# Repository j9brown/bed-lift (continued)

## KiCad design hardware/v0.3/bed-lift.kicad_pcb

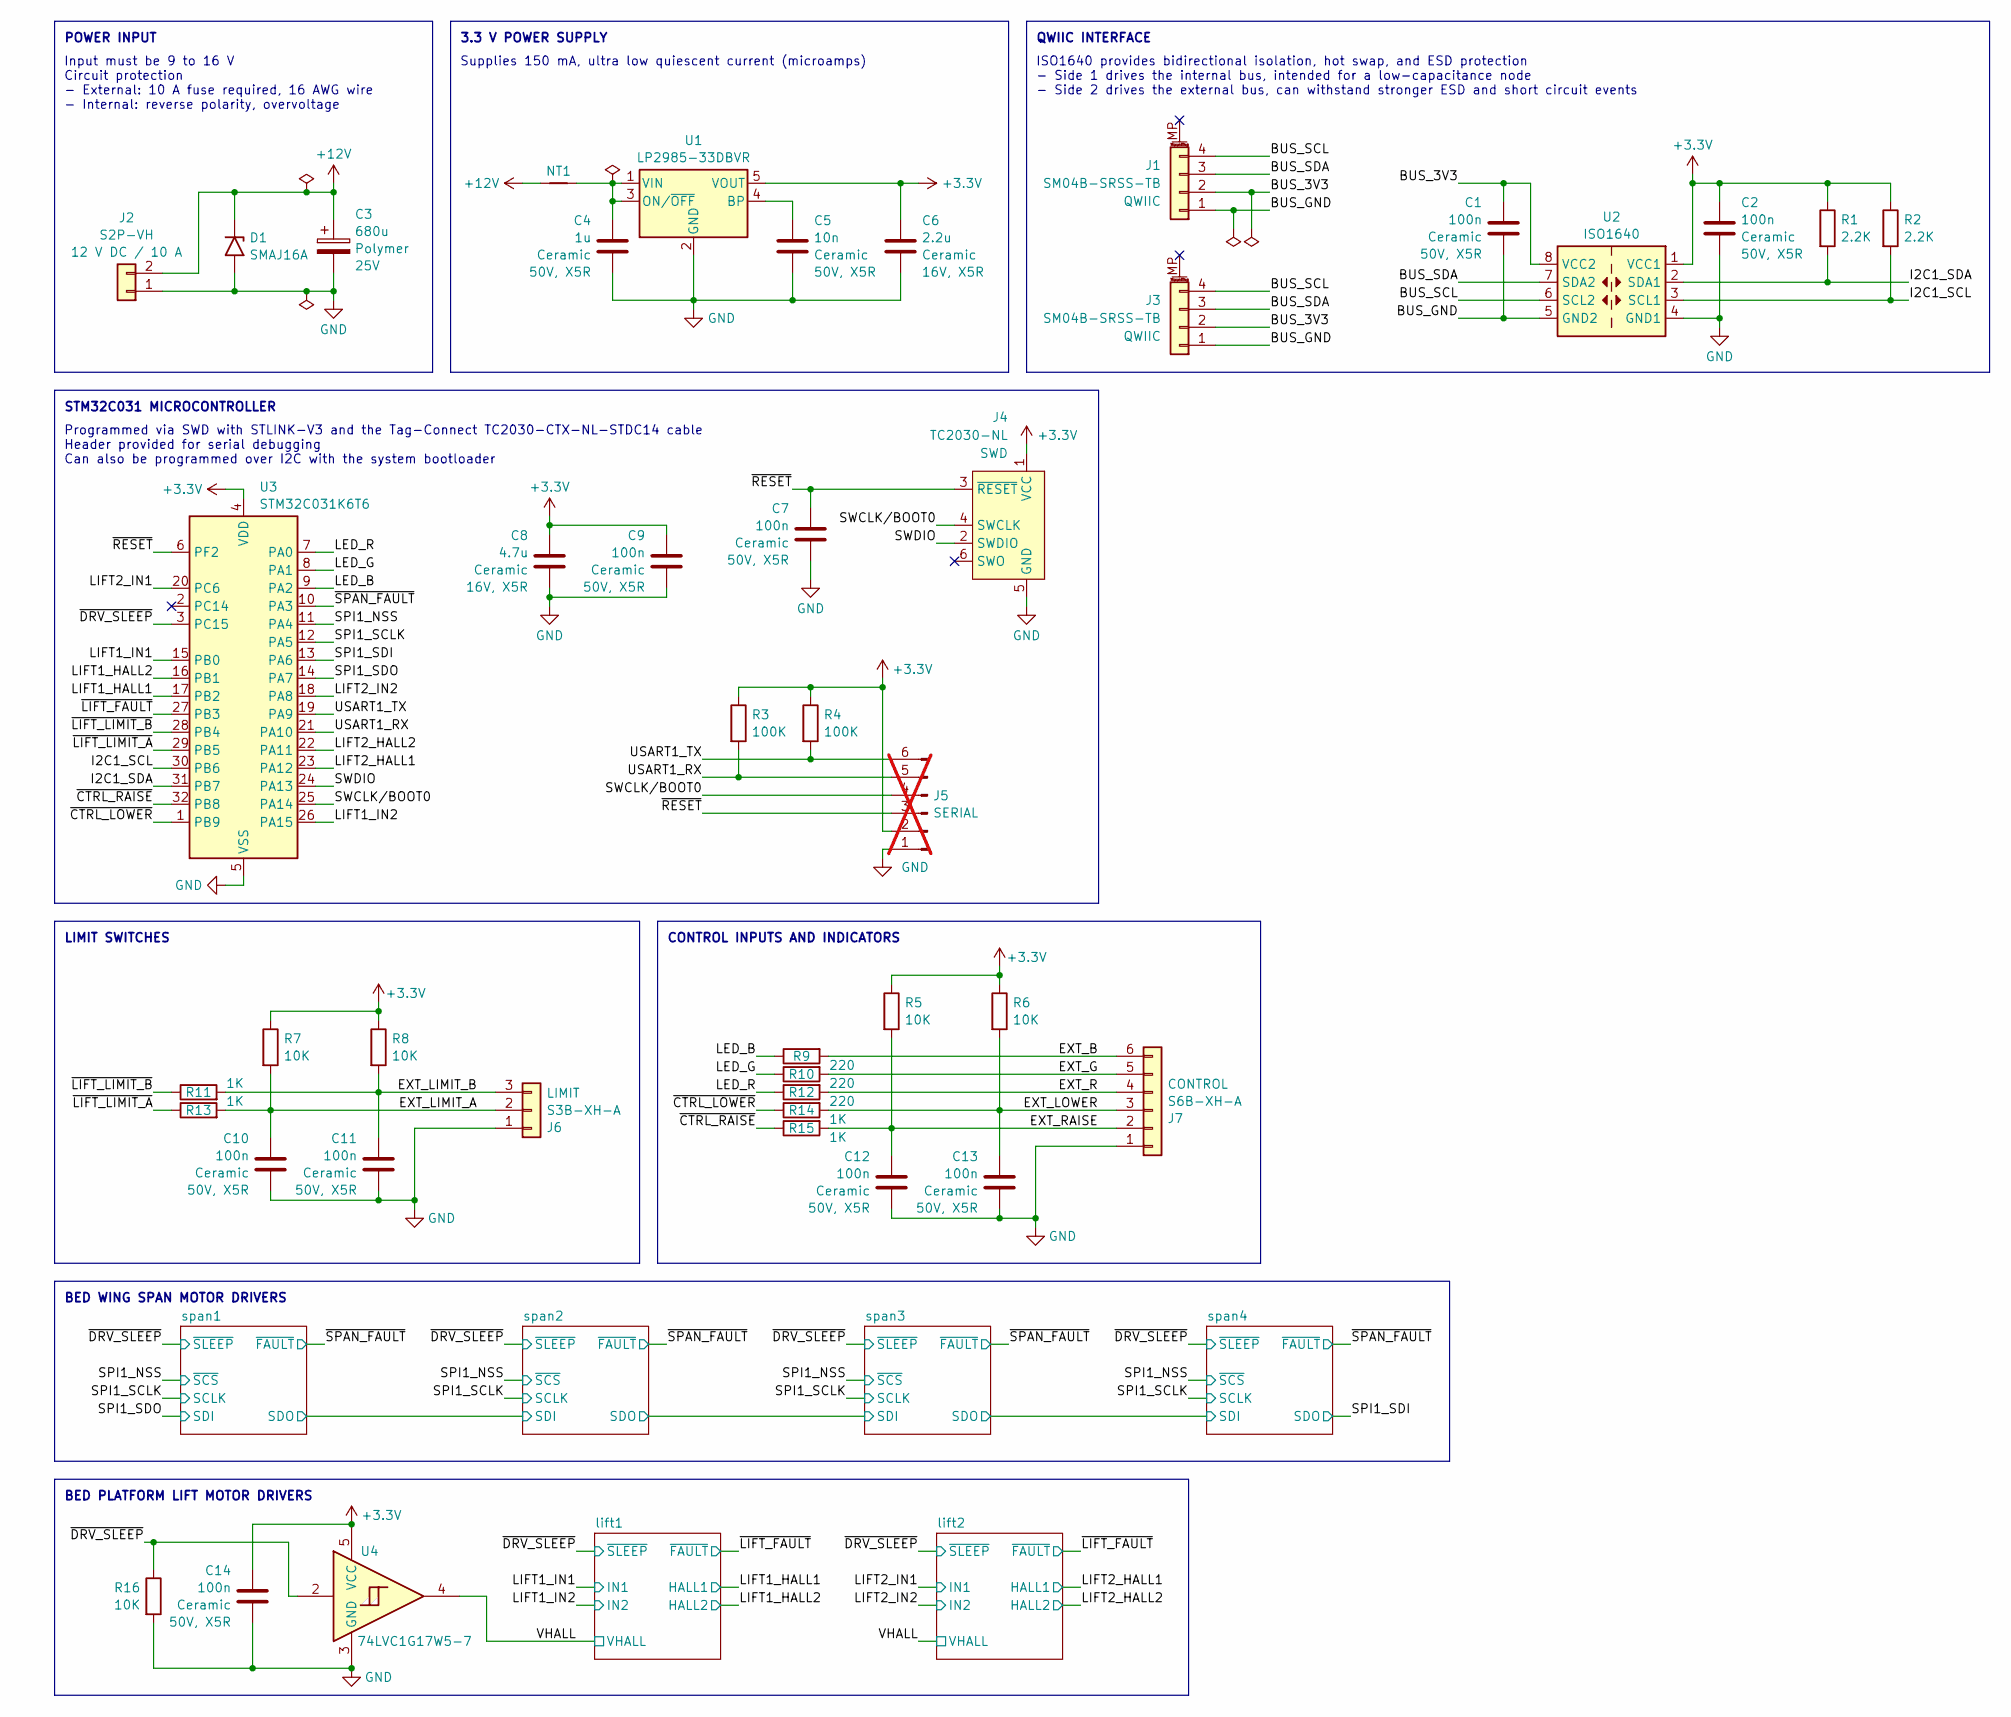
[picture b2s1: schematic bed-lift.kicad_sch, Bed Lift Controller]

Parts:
C1, C2, C7, C9, C10, C11, C12, C13, C14: 100n; C_0603_1608Metric; Rating 50V, X5R; LCSC C14663
C3: 680u; CP_Radial_D8.0mm_P3.50mm; Rating 25V; LCSC C5243855
C4: 1u; C_0603_1608Metric; Rating 50V, X5R; LCSC C15849
C5: 10n; C_0603_1608Metric; Rating 50V, X5R; LCSC C57112
C6: 2.2u; C_0603_1608Metric; Rating 16V, X5R; LCSC C23630
C8: 4.7u; C_0603_1608Metric; Rating 16V, X5R; LCSC C19666
D1: SMAJ16A; D_SMA; LCSC C74561
J1, J3: SM04B-SRSS-TB; JST_SH_SM04B-SRSS-TB_1x04-1MP_P1.00mm_Horizontal; LCSC C160404
J2: S2P-VH; JST_VH_S2P-VH_1x02_P3.96mm_Horizontal; LCSC C160355
J4: TC2030-NL; Tag-Connect_TC2030-IDC-NL_2x03_P1.27mm_Vertical
J5: PH1-06-UA; PinHeader_1x06_P2.54mm_Vertical; not fitted
J6: S3B-XH-A; JST_XH_S3B-XH-A_1x03_P2.50mm_Horizontal; LCSC C157928
J7: S6B-XH-A; JST_XH_S6B-XH-A_1x06_P2.50mm_Horizontal; LCSC C157919
NT1: NetTie_2; NetTie-2_SMD_Pad0.4mm
R1, R2: 2.2K; R_0603_1608Metric; LCSC C4190
R3, R4: 100K; R_0603_1608Metric; LCSC C25803
R5, R6, R7, R8, R16: 10K; R_0603_1608Metric; LCSC C25804
R9, R10, R12: 220; R_0603_1608Metric; LCSC C22962
R11, R13, R14, R15: 1K; R_0603_1608Metric; LCSC C21190
U1: LP2985-33DBVR; SOT-23-5; LCSC C95414
U2: ISO1640; SOIC-8_3.9x4.9mm_P1.27mm; LCSC C5122339
U3: STM32C031K6T6; LQFP-32_7x7mm_P0.8mm; LCSC C5456169
U4: 74LVC1G17W5-7; SOT-23-5; LCSC C151394

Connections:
+3.3V: C2.1, C6.2, C8.1, C9.1, C14.1, J4.1 (VCC), J5.2, R1.1, R2.1, R3.1, R4.1, R5.1, R6.1, R7.1, R8.1, U1.5 (VOUT), U2.1 (VCC1), U3.4 (VDD), U4.5 (VCC); also elsewhere on the board
+12V: C3.1, D1.1 (A1), J2.2, NT1.1; also elsewhere on the board
/BUS_3V3: C1.1, J1.2, J3.2, U2.8 (VCC2)
/BUS_GND: C1.2, J1.1, J3.1, U2.5 (GND2)
/BUS_SCL: J1.4, J3.4, U2.6 (SCL2)
/BUS_SDA: J1.3, J3.3, U2.7 (SDA2)
/EXT_B: J7.6, R9.2
/EXT_G: J7.5, R10.2
/EXT_LIMIT_A: C10.1, J6.2, R7.2, R13.2
/EXT_LIMIT_B: C11.1, J6.3, R8.2, R11.2
/EXT_LOWER: C13.1, J7.3, R6.2, R14.2
/EXT_R: J7.4, R12.2
/EXT_RAISE: C12.1, J7.2, R5.2, R15.2
/I2C1_SCL: R2.2, U2.3 (SCL1), U3.30 (PB6)
/I2C1_SDA: R1.2, U2.2 (SDA1), U3.31 (PB7)
/LED_B: R9.1, U3.9 (PA2)
/LED_G: R10.1, U3.8 (PA1)
/LED_R: R12.1, U3.7 (PA0)
/LIFT1_HALL1: U3.17 (PB2); also elsewhere on the board
/LIFT1_HALL2: U3.16 (PB1); also elsewhere on the board
/LIFT1_IN1: U3.15 (PB0); also elsewhere on the board
/LIFT1_IN2: U3.26 (PA15); also elsewhere on the board
/LIFT2_HALL1: U3.23 (PA12); also elsewhere on the board
/LIFT2_HALL2: U3.22 (PA11); also elsewhere on the board
/LIFT2_IN1: U3.20 (PC6); also elsewhere on the board
/LIFT2_IN2: U3.18 (PA8); also elsewhere on the board
/SPI1_NSS: U3.11 (PA4); also elsewhere on the board
/SPI1_SCLK: U3.12 (PA5); also elsewhere on the board
/SPI1_SDI: U3.13 (PA6); also elsewhere on the board
/SPI1_SDO: U3.14 (PA7); also elsewhere on the board
/SWCLK/BOOT0: J4.4 (SWCLK), J5.4, U3.25 (PA14)
/SWDIO: J4.2 (SWDIO), U3.24 (PA13)
/USART1_RX: J5.5, R3.2, U3.21 (PA10)
/USART1_TX: J5.6, R4.2, U3.19 (PA9)
/VHALL: U4.4; also elsewhere on the board
/~CTRL_LOWER: R14.1, U3.1 (PB9)
/~CTRL_RAISE: R15.1, U3.32 (PB8)
/~DRV_SLEEP: R16.1, U3.3 (PC15), U4.2; also elsewhere on the board
/~LIFT_FAULT: U3.27 (PB3); also elsewhere on the board
/~LIFT_LIMIT_A: R13.1, U3.29 (PB5)
/~LIFT_LIMIT_B: R11.1, U3.28 (PB4)
/~RESET: C7.1, J4.3 (~RESET), J5.3, U3.6 (PF2)
/~SPAN_FAULT: U3.10 (PA3); also elsewhere on the board
GND: C2.2, C3.2, C4.2, C5.1, C6.1, C7.2, C8.2, C9.2, C10.2, C11.2, C12.2, C13.2, C14.2, D1.2 (A2), J2.1, J4.5 (GND), J5.1, J6.1, J7.1, R16.2, U1.2 (GND), U2.4 (GND1), U3.5 (VSS), U4.3 (GND); also elsewhere on the board
unnamed: C5.2, U1.4 (BP)
unnamed: C4.1, NT1.2, U1.1 (VIN), U1.3 (ON/~OFF)

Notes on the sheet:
Programmed via SWD with STLINK-V3 and the Tag-Connect TC2030-CTX-NL-STDC14 cable Header provided for serial debugging Can also be programmed over I2C with the system bootloader
Supplies 150 mA, ultra low quiescent current (microamps)
LIMIT SWITCHES
POWER INPUT
BED WING SPAN MOTOR DRIVERS
STM32C031 MICROCONTROLLER
3.3 V POWER SUPPLY
QWIIC INTERFACE
CONTROL INPUTS AND INDICATORS
Input must be 9 to 16 V Circuit protection - External: 10 A fuse required, 16 AWG wire - Internal: reverse polarity, overvoltage
ISO1640 provides bidirectional isolation, hot swap, and ESD protection - Side 1 drives the internal bus, intended for a low-capacitance node - Side 2 drives the external bus, can withstand stronger ESD and short circuit events
BED PLATFORM LIFT MOTOR DRIVERS

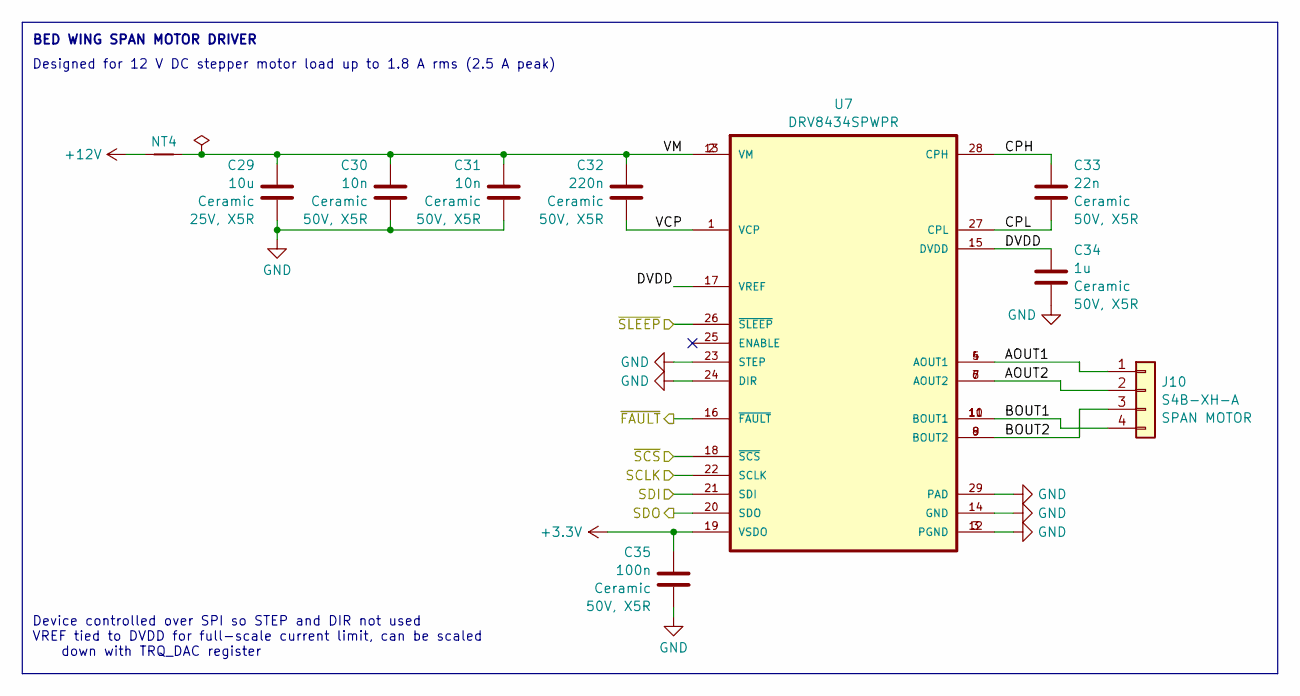
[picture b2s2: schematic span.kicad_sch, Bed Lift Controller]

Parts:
C29: 10u; C_0805_2012Metric; Rating 25V, X5R; LCSC C15850
C30, C31: 10n; C_0603_1608Metric; Rating 50V, X5R; LCSC C57112
C32: 220n; C_0603_1608Metric; Rating 50V, X5R; LCSC C1603
C33: 22n; C_0603_1608Metric; Rating 50V, X5R; LCSC C21122
C34: 1u; C_0603_1608Metric; Rating 50V, X5R; LCSC C15849
C35: 100n; C_0603_1608Metric; Rating 50V, X5R; LCSC C14663
J10: S4B-XH-A; JST_XH_S4B-XH-A_1x04_P2.50mm_Horizontal; LCSC C157925
NT4: NetTie_2; NetTie-2_SMD_Pad1.5mm
U7: DRV8434SPWPR; HTSSOP-28 PWP0028M; LCSC C3681202

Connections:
+3.3V: C35.1, U7.19 (VSDO); also elsewhere on the board
+12V: NT4.1; also elsewhere on the board
/SPI1_NSS: U7.18 (~SCS); also elsewhere on the board
/SPI1_SCLK: U7.22 (SCLK); also elsewhere on the board
/SPI1_SDO: U7.21 (SDI); also elsewhere on the board
/span1/AOUT1: J10.1, U7.4 (AOUT1), U7.5 (AOUT1)
/span1/AOUT2: J10.2, U7.6 (AOUT2), U7.7 (AOUT2)
/span1/BOUT1: J10.4, U7.10 (BOUT1), U7.11 (BOUT1)
/span1/BOUT2: J10.3, U7.8 (BOUT2), U7.9 (BOUT2)
/span1/CPH: C33.1, U7.28 (CPH)
/span1/CPL: C33.2, U7.27 (CPL)
/span1/DVDD: C34.1, U7.15 (DVDD), U7.17 (VREF)
/span1/SDO: U7.20 (SDO); also elsewhere on the board
/span1/VCP: C32.2, U7.1 (VCP)
/span1/VM: C29.2, C30.1, C31.1, C32.1, NT4.2, U7.2 (VM), U7.13 (VM)
/~DRV_SLEEP: U7.26 (~SLEEP); also elsewhere on the board
/~SPAN_FAULT: U7.16 (~FAULT); also elsewhere on the board
GND: C29.1, C30.2, C31.2, C34.2, C35.2, U7.3 (PGND), U7.12 (PGND), U7.14 (GND), U7.23 (STEP), U7.24 (DIR), U7.29 (PAD); also elsewhere on the board

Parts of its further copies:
C36, C43, C50: 10u; C_0805_2012Metric; Rating 25V, X5R; LCSC C15850
C37, C38, C44, C45, C51, C52: 10n; C_0603_1608Metric; Rating 50V, X5R; LCSC C57112
C39, C46, C53: 220n; C_0603_1608Metric; Rating 50V, X5R; LCSC C1603
C40, C47, C54: 22n; C_0603_1608Metric; Rating 50V, X5R; LCSC C21122
C41, C48, C55: 1u; C_0603_1608Metric; Rating 50V, X5R; LCSC C15849
C42, C49, C56: 100n; C_0603_1608Metric; Rating 50V, X5R; LCSC C14663
J11, J12, J13: S4B-XH-A; JST_XH_S4B-XH-A_1x04_P2.50mm_Horizontal; LCSC C157925
NT5, NT6, NT7: NetTie_2; NetTie-2_SMD_Pad1.5mm
U8, U9, U10: DRV8434SPWPR; HTSSOP-28 PWP0028M; LCSC C3681202

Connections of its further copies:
+3.3V: C42.1, C49.1, C56.1, U8.19 (VSDO), U9.19 (VSDO), U10.19 (VSDO); also elsewhere on the board
+12V: NT5.1, NT6.1, NT7.1; also elsewhere on the board
/SPI1_NSS: U8.18 (~SCS), U9.18 (~SCS), U10.18 (~SCS); also elsewhere on the board
/SPI1_SCLK: U8.22 (SCLK), U9.22 (SCLK), U10.22 (SCLK); also elsewhere on the board
/SPI1_SDI: U10.20 (SDO); also elsewhere on the board
/span1/SDO: U8.21 (SDI); also elsewhere on the board
/span2/AOUT1: J11.1, U8.4 (AOUT1), U8.5 (AOUT1)
/span2/AOUT2: J11.2, U8.6 (AOUT2), U8.7 (AOUT2)
/span2/BOUT1: J11.4, U8.10 (BOUT1), U8.11 (BOUT1)
/span2/BOUT2: J11.3, U8.8 (BOUT2), U8.9 (BOUT2)
/span2/CPH: C40.1, U8.28 (CPH)
/span2/CPL: C40.2, U8.27 (CPL)
/span2/DVDD: C41.1, U8.15 (DVDD), U8.17 (VREF)
/span2/SDO: U8.20 (SDO), U9.21 (SDI)
/span2/VCP: C39.2, U8.1 (VCP)
/span2/VM: C36.2, C37.1, C38.1, C39.1, NT5.2, U8.2 (VM), U8.13 (VM)
/span3/AOUT1: J12.1, U9.4 (AOUT1), U9.5 (AOUT1)
/span3/AOUT2: J12.2, U9.6 (AOUT2), U9.7 (AOUT2)
/span3/BOUT1: J12.4, U9.10 (BOUT1), U9.11 (BOUT1)
/span3/BOUT2: J12.3, U9.8 (BOUT2), U9.9 (BOUT2)
/span3/CPH: C47.1, U9.28 (CPH)
/span3/CPL: C47.2, U9.27 (CPL)
/span3/DVDD: C48.1, U9.15 (DVDD), U9.17 (VREF)
/span3/SDO: U9.20 (SDO), U10.21 (SDI)
/span3/VCP: C46.2, U9.1 (VCP)
/span3/VM: C43.2, C44.1, C45.1, C46.1, NT6.2, U9.2 (VM), U9.13 (VM)
/span4/AOUT1: J13.1, U10.4 (AOUT1), U10.5 (AOUT1)
/span4/AOUT2: J13.2, U10.6 (AOUT2), U10.7 (AOUT2)
/span4/BOUT1: J13.4, U10.10 (BOUT1), U10.11 (BOUT1)
/span4/BOUT2: J13.3, U10.8 (BOUT2), U10.9 (BOUT2)
/span4/CPH: C54.1, U10.28 (CPH)
/span4/CPL: C54.2, U10.27 (CPL)
/span4/DVDD: C55.1, U10.15 (DVDD), U10.17 (VREF)
/span4/VCP: C53.2, U10.1 (VCP)
/span4/VM: C50.2, C51.1, C52.1, C53.1, NT7.2, U10.2 (VM), U10.13 (VM)
/~DRV_SLEEP: U8.26 (~SLEEP), U9.26 (~SLEEP), U10.26 (~SLEEP); also elsewhere on the board
/~SPAN_FAULT: U8.16 (~FAULT), U9.16 (~FAULT), U10.16 (~FAULT); also elsewhere on the board
GND: C36.1, C37.2, C38.2, C41.2, C42.2, C43.1, C44.2, C45.2, C48.2, C49.2, C50.1, C51.2, C52.2, C55.2, C56.2, U8.3 (PGND), U8.12 (PGND), U8.14 (GND), U8.23 (STEP), U8.24 (DIR), U8.29 (PAD), U9.3 (PGND), U9.12 (PGND), U9.14 (GND), U9.23 (STEP), U9.24 (DIR), U9.29 (PAD), U10.3 (PGND), U10.12 (PGND), U10.14 (GND), U10.23 (STEP), U10.24 (DIR), U10.29 (PAD); also elsewhere on the board

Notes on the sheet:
Designed for 12 V DC stepper motor load up to 1.8 A rms (2.5 A peak)
BED WING SPAN MOTOR DRIVER
Device controlled over SPI so STEP and DIR not used VREF tied to DVDD for full-scale current limit, can be scaled down with TRQ_DAC register

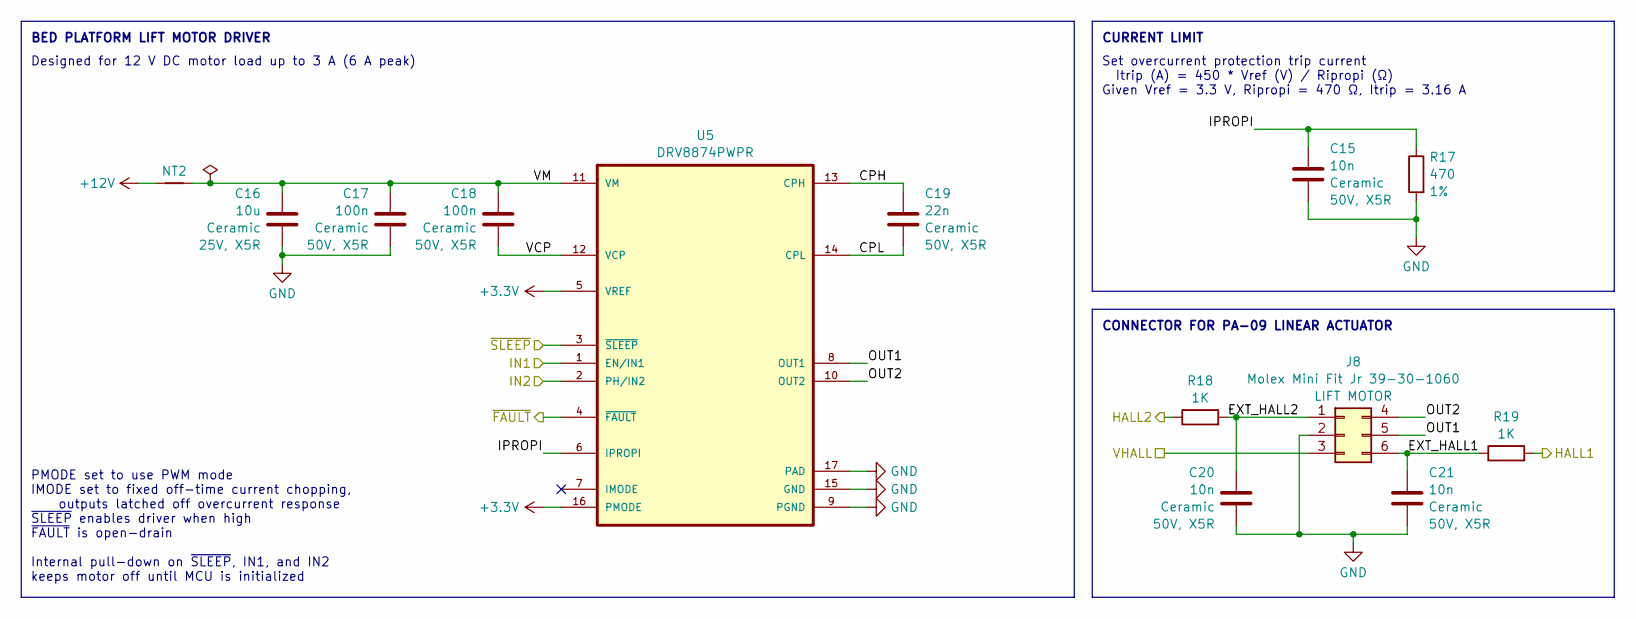
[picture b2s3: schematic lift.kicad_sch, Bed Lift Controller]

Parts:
C15, C20, C21: 10n; C_0603_1608Metric; Rating 50V, X5R; LCSC C57112
C16: 10u; C_0805_2012Metric; Rating 25V, X5R; LCSC C15850
C17, C18: 100n; C_0603_1608Metric; Rating 50V, X5R; LCSC C14663
C19: 22n; C_0603_1608Metric; Rating 50V, X5R; LCSC C21122
J8: Molex Mini Fit Jr 39-30-1060; MOLEX_39301060; LCSC C114098
NT2: NetTie_2; NetTie-2_SMD_Pad2.5mm
R17: 470; R_0603_1608Metric; Rating 1%; LCSC C23179
R18, R19: 1K; R_0603_1608Metric; LCSC C21190
U5: DRV8874PWPR; HTSSOP-16 PWP0016J; LCSC C1855818

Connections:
+3.3V: U5.5 (VREF), U5.16 (PMODE); also elsewhere on the board
+12V: NT2.1; also elsewhere on the board
/LIFT1_HALL1: R19.2; also elsewhere on the board
/LIFT1_HALL2: R18.1; also elsewhere on the board
/LIFT1_IN1: U5.1 (EN/IN1); also elsewhere on the board
/LIFT1_IN2: U5.2 (PH/IN2); also elsewhere on the board
/VHALL: J8.3; also elsewhere on the board
/lift1/CPH: C19.1, U5.13 (CPH)
/lift1/CPL: C19.2, U5.14 (CPL)
/lift1/EXT_HALL1: C21.1, J8.6, R19.1
/lift1/EXT_HALL2: C20.1, J8.1, R18.2
/lift1/IPROPI: C15.1, R17.1, U5.6 (IPROPI)
/lift1/OUT1: J8.5, U5.8 (OUT1)
/lift1/OUT2: J8.4, U5.10 (OUT2)
/lift1/VCP: C18.2, U5.12 (VCP)
/lift1/VM: C16.2, C17.1, C18.1, NT2.2, U5.11 (VM)
/~DRV_SLEEP: U5.3 (~SLEEP); also elsewhere on the board
/~LIFT_FAULT: U5.4 (~FAULT); also elsewhere on the board
GND: C15.2, C16.1, C17.2, C20.2, C21.2, J8.2, R17.2, U5.9 (PGND), U5.15 (GND), U5.17 (PAD); also elsewhere on the board

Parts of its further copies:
C22, C27, C28: 10n; C_0603_1608Metric; Rating 50V, X5R; LCSC C57112
C23: 10u; C_0805_2012Metric; Rating 25V, X5R; LCSC C15850
C24, C25: 100n; C_0603_1608Metric; Rating 50V, X5R; LCSC C14663
C26: 22n; C_0603_1608Metric; Rating 50V, X5R; LCSC C21122
J9: Molex Mini Fit Jr 39-30-1060; MOLEX_39301060; LCSC C114098
NT3: NetTie_2; NetTie-2_SMD_Pad2.5mm
R20: 470; R_0603_1608Metric; Rating 1%; LCSC C23179
R21, R22: 1K; R_0603_1608Metric; LCSC C21190
U6: DRV8874PWPR; HTSSOP-16 PWP0016J; LCSC C1855818

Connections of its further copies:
+3.3V: U6.5 (VREF), U6.16 (PMODE); also elsewhere on the board
+12V: NT3.1; also elsewhere on the board
/LIFT2_HALL1: R22.2; also elsewhere on the board
/LIFT2_HALL2: R21.1; also elsewhere on the board
/LIFT2_IN1: U6.1 (EN/IN1); also elsewhere on the board
/LIFT2_IN2: U6.2 (PH/IN2); also elsewhere on the board
/VHALL: J9.3; also elsewhere on the board
/lift2/CPH: C26.1, U6.13 (CPH)
/lift2/CPL: C26.2, U6.14 (CPL)
/lift2/EXT_HALL1: C28.1, J9.6, R22.1
/lift2/EXT_HALL2: C27.1, J9.1, R21.2
/lift2/IPROPI: C22.1, R20.1, U6.6 (IPROPI)
/lift2/OUT1: J9.5, U6.8 (OUT1)
/lift2/OUT2: J9.4, U6.10 (OUT2)
/lift2/VCP: C25.2, U6.12 (VCP)
/lift2/VM: C23.2, C24.1, C25.1, NT3.2, U6.11 (VM)
/~DRV_SLEEP: U6.3 (~SLEEP); also elsewhere on the board
/~LIFT_FAULT: U6.4 (~FAULT); also elsewhere on the board
GND: C22.2, C23.1, C24.2, C27.2, C28.2, J9.2, R20.2, U6.9 (PGND), U6.15 (GND), U6.17 (PAD); also elsewhere on the board

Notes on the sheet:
CONNECTOR FOR PA-09 LINEAR ACTUATOR
PMODE set to use PWM mode IMODE set to fixed off-time current chopping, outputs latched off overcurrent response ~{SLEEP} enables driver when high ~{FAULT} is open-drain Internal pull-down on ~{SLEEP}, IN1, and IN2 keeps motor off until MCU is initialized
BED PLATFORM LIFT MOTOR DRIVER
CURRENT LIMIT
Designed for 12 V DC motor load up to 3 A (6 A peak)
Set overcurrent protection trip current Itrip (A) = 450 * Vref (V) / Ripropi (Ω) Given Vref = 3.3 V, Ripropi = 470 Ω, Itrip = 3.16 A

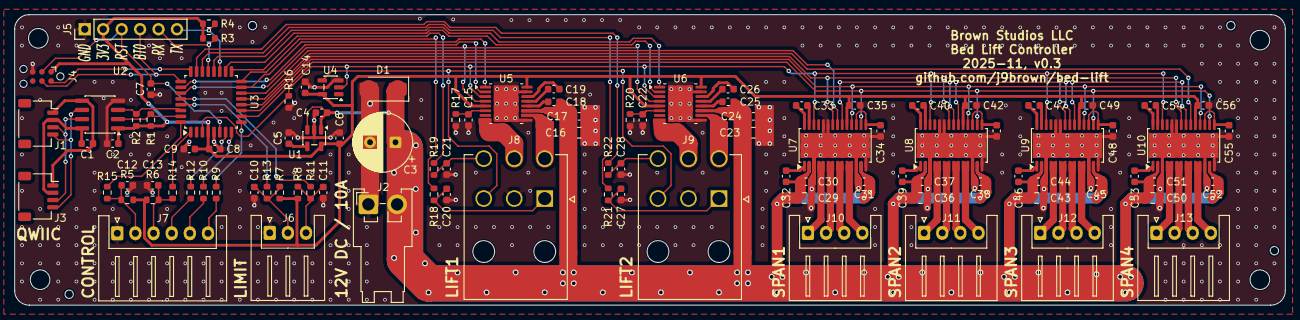
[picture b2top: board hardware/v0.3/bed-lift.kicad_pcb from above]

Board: 4 copper layers, 175.0 x 40.0 mm, 117 parts (1 on the bottom side), 103 nets.

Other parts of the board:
MP1, MP2, MP3, MP4: MountingHole_2.7mm_M2.5
TH1, TH1#2, TH1#3, TH1#4: JLCPCB_PCBA_Tooling_Hole

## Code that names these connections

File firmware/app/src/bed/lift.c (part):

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#define LIFT_LIMIT_DEBOUNCE_MS (50)
#define LIFT_LIMIT_DEBOUNCE_CYCLES (uint32_t)((uint64_t)CONFIG_SYS_CLOCK_HW_CYCLES_PER_SEC * LIFT_LIMIT_DEBOUNCE_MS / 1000)

static const struct gpio_dt_spec lift_limit_a_gpio = GPIO_DT_SPEC_GET(ZEPHYR_USER_NODE, lift_limit_a_gpios);
static const struct gpio_dt_spec lift_limit_b_gpio = GPIO_DT_SPEC_GET(ZEPHYR_USER_NODE, lift_limit_b_gpios);

enum lift_limit_state {
    LIFT_LIMIT_BELOW_SAFE_ZONE = 0b11,
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// This function must be called on every timer tick (before the cycle counter rolls over).
static void lift_limit_update_l(uint32_t cycle) {
    gpio_port_value_t value = 0;
    gpio_port_get(lift_limit_a_gpio.port, &value);
    enum lift_limit_state state =
            (IS_BIT_SET(value, lift_limit_a_gpio.pin) ? 0b01 : 0) |
            (IS_BIT_SET(value, lift_limit_b_gpio.pin) ? 0b10 : 0);
    if (state != lift_limit_data.raw_state) {
        lift_limit_data.raw_state = state;
        lift_limit_data.raw_change_cycle = cycle;
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
#define LIFT_HALL_PULSES_PER_INCH (660)

static const struct gpio_dt_spec lift1_hall1_gpio = GPIO_DT_SPEC_GET(ZEPHYR_USER_NODE, lift1_hall1_gpios);
static const struct gpio_dt_spec lift1_hall2_gpio = GPIO_DT_SPEC_GET(ZEPHYR_USER_NODE, lift1_hall2_gpios);
static const struct gpio_dt_spec lift2_hall1_gpio = GPIO_DT_SPEC_GET(ZEPHYR_USER_NODE, lift2_hall1_gpios);
static const struct gpio_dt_spec lift2_hall2_gpio = GPIO_DT_SPEC_GET(ZEPHYR_USER_NODE, lift2_hall2_gpios);

struct lift_hall_data {
    struct gpio_callback gpio_callback;
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    gpio_port_value_t value = 0;
    gpio_port_get(port, &value);
    unsigned bits =
            (IS_BIT_SET(value, lift1_hall1_gpio.pin) ? 0b10 : 0) |
            (IS_BIT_SET(value, lift1_hall2_gpio.pin) ? 0b01 : 0);
    atomic_add(&lift1_hall_data.isr_position, LIFT_HALL_QUADRATURE[(lift1_hall_data.isr_bits << 2) | bits]);
    lift1_hall_data.isr_bits = bits;
}
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    gpio_port_value_t value = 0;
    gpio_port_get(port, &value);
    unsigned bits =
            (IS_BIT_SET(value, lift2_hall1_gpio.pin) ? 0b10 : 0) |
            (IS_BIT_SET(value, lift2_hall2_gpio.pin) ? 0b01 : 0);
    atomic_add(&lift2_hall_data.isr_position, LIFT_HALL_QUADRATURE[(lift2_hall_data.isr_bits << 2) | bits]);
    lift2_hall_data.isr_bits = bits;
}
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 * LIFT MOTOR CONTROLLER
 */

static const struct gpio_dt_spec lift_fault_gpio = GPIO_DT_SPEC_GET(ZEPHYR_USER_NODE, lift_fault_gpios);
static const struct gpio_dt_spec lift_sleep_gpio = GPIO_DT_SPEC_GET(ZEPHYR_USER_NODE, lift_sleep_gpios);

#define LIFT_IN_TIMER_NUMBER 1
#define LIFT_IN_TIMER_NODE DT_NODELABEL(_CONCAT(timers, LIFT_IN_TIMER_NUMBER))
#define LIFT_IN_TIMER _CONCAT(TIM, LIFT_IN_TIMER_NUMBER)

static const struct pwm_dt_spec lift1_in1_pwm = PWM_DT_SPEC_GET_BY_IDX(DT_NODELABEL(lift1_in1), 0);
static const struct pwm_dt_spec lift1_in2_pwm = PWM_DT_SPEC_GET_BY_IDX(DT_NODELABEL(lift1_in2), 0);
static const struct pwm_dt_spec lift2_in1_pwm = PWM_DT_SPEC_GET_BY_IDX(DT_NODELABEL(lift2_in1), 0);
static const struct pwm_dt_spec lift2_in2_pwm = PWM_DT_SPEC_GET_BY_IDX(DT_NODELABEL(lift2_in2), 0);

static const struct device *lift_loop_tick_dev = DEVICE_DT_GET(DT_NODELABEL(lift_loop_tick));

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static struct lift_loop_data lift_loop_data;

static int lift_has_fault(void) {
	return gpio_pin_get_dt(&lift_fault_gpio);
}

static void lift_loop_tick_handler(const struct device *dev, void *user_data) {
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
int lift_init(void) {
    int err;
    const struct device *lift_fault_port = lift_fault_gpio.port;
    const struct device *lift_sleep_port = lift_sleep_gpio.port;
    const struct device *lift_limit_port = lift_limit_a_gpio.port;
    const struct device *lift1_hall_port = lift1_hall1_gpio.port;
    const struct device *lift2_hall_port = lift2_hall1_gpio.port;
    const struct device *lift_in_dev = lift1_in1_pwm.dev;
    const uint32_t lift_in_period_ns = lift1_in1_pwm.period;
    if (lift_limit_port != lift_limit_b_gpio.port ||
            lift1_hall_port != lift1_hall2_gpio.port ||
            lift2_hall_port != lift2_hall2_gpio.port ||
            lift1_in2_pwm.dev != lift_in_dev || lift1_in2_pwm.period != lift_in_period_ns ||
            lift2_in1_pwm.dev != lift_in_dev || lift2_in1_pwm.period != lift_in_period_ns ||
            lift2_in2_pwm.dev != lift_in_dev || lift2_in2_pwm.period != lift_in_period_ns) {
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            !device_is_ready(lift_in_dev)) {
        return -ENODEV;
    }
    if ((err = gpio_pin_configure_dt(&lift_fault_gpio, GPIO_INPUT)) ||
            (err = gpio_pin_configure_dt(&lift_sleep_gpio, GPIO_OUTPUT_ACTIVE)) ||
            (err = gpio_pin_configure_dt(&lift_limit_a_gpio, GPIO_INPUT)) ||
            (err = gpio_pin_configure_dt(&lift_limit_b_gpio, GPIO_INPUT)) ||
            (err = gpio_pin_configure_dt(&lift1_hall1_gpio, GPIO_INPUT)) ||
            (err = gpio_pin_configure_dt(&lift1_hall2_gpio, GPIO_INPUT)) ||
            (err = gpio_pin_configure_dt(&lift2_hall1_gpio, GPIO_INPUT)) ||
            (err = gpio_pin_configure_dt(&lift2_hall2_gpio, GPIO_INPUT))) {
        return err;
    }
    if ((err = gpio_pin_interrupt_configure_dt(&lift1_hall1_gpio, GPIO_INT_EDGE_BOTH)) ||
            (err = gpio_pin_interrupt_configure_dt(&lift1_hall2_gpio, GPIO_INT_EDGE_BOTH)) ||
            (err = gpio_pin_interrupt_configure_dt(&lift2_hall1_gpio, GPIO_INT_EDGE_BOTH)) ||
            (err = gpio_pin_interrupt_configure_dt(&lift2_hall2_gpio, GPIO_INT_EDGE_BOTH))) {
        return err;
    }
    gpio_init_callback(&lift1_hall_data.gpio_callback, lift1_hall_gpio_handler,
        BIT(lift1_hall1_gpio.pin) | BIT(lift1_hall2_gpio.pin));
    gpio_init_callback(&lift2_hall_data.gpio_callback, lift2_hall_gpio_handler,
        BIT(lift2_hall1_gpio.pin) | BIT(lift2_hall2_gpio.pin));
    lift1_hall_gpio_handler(lift1_hall_port, &lift1_hall_data.gpio_callback,
            lift1_hall_data.gpio_callback.pin_mask);
    lift2_hall_gpio_handler(lift2_hall_port, &lift2_hall_data.gpio_callback,
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    K_SPINLOCK(&lift_lock) {
        lift_loop_halt_l();
    }
    gpio_pin_set_dt(&lift_sleep_gpio, true);
    power_5v_release(POWER_DEMAND_LIFT);
    lift_action_state = LIFT_ACTION_SLEEP_DONE;
    return 0;
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    K_SPINLOCK(&lift_lock) {
        if (lift_action_state != LIFT_ACTION_MOVE_PREPARE && lift_action_state != LIFT_ACTION_MOVE_TRAVEL) {
            power_5v_request(POWER_DEMAND_LIFT);
            gpio_pin_set_dt(&lift_sleep_gpio, false);
            lift_loop_halt_l();
            lift_action_state = LIFT_ACTION_MOVE_PREPARE;
            lift_prepare_start_cycle = k_cycle_get_32();
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
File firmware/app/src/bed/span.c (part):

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// To test, set the initial speed to some value and the acceleration to zero.
// If the motor stalls prematurely, then lower the threshold.
// If the motor makes a lot of noise when reaching the end stop, then raise the threshold.
// If the span makes a metallic sound when starting and stopping, check the screw tension on the drive arms.
static inline uint16_t span_stall_threshold(unsigned speed) {
    if (SPAN_DEBUG_STALL_DETECTION_DISABLED) {
        return 0;
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
#define ZEPHYR_USER_NODE DT_PATH(zephyr_user)

static const struct gpio_dt_spec span1_limit_a_gpio = GPIO_DT_SPEC_GET(ZEPHYR_USER_NODE, span1_limit_a_gpios);
static const struct gpio_dt_spec span1_limit_b_gpio = GPIO_DT_SPEC_GET(ZEPHYR_USER_NODE, span1_limit_b_gpios);
static const struct gpio_dt_spec span2_limit_a_gpio = GPIO_DT_SPEC_GET(ZEPHYR_USER_NODE, span2_limit_a_gpios);
static const struct gpio_dt_spec span2_limit_b_gpio = GPIO_DT_SPEC_GET(ZEPHYR_USER_NODE, span2_limit_b_gpios);

#define SPAN_LIMIT_STATE_1A_INDEX (0)
#define SPAN_LIMIT_STATE_1A (BIT(SPAN_LIMIT_STATE_1A_INDEX))
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// This function must be called on every timer tick (before the cycle counter rolls over).
static void span_limit_update_l(uint32_t cycle) {
    gpio_port_value_t value = 0;
    gpio_port_get(span1_limit_a_gpio.port, &value);
    span_limit_update_bit_l(cycle, SPAN_LIMIT_STATE_1A_INDEX, IS_BIT_SET(value, span1_limit_a_gpio.pin), "1A");
    span_limit_update_bit_l(cycle, SPAN_LIMIT_STATE_1B_INDEX, IS_BIT_SET(value, span1_limit_b_gpio.pin), "1B");
    span_limit_update_bit_l(cycle, SPAN_LIMIT_STATE_2A_INDEX, IS_BIT_SET(value, span2_limit_a_gpio.pin), "2A");
    span_limit_update_bit_l(cycle, SPAN_LIMIT_STATE_2B_INDEX, IS_BIT_SET(value, span2_limit_b_gpio.pin), "2B");
    span_limit_data.seen |= span_limit_data.state;
}

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#define SPAN_STEP_TIMER_CHANNEL LL_TIM_CHANNEL_CH1
#define SPAN_STEP_TIMER _CONCAT(TIM, SPAN_STEP_TIMER_NUMBER)

static const struct pwm_dt_spec span_step_pwm = PWM_DT_SPEC_GET_BY_IDX(DT_NODELABEL(span_step), 0);

// The maximum and minimum step rate in pulses per second.
// The maximum is limited by interrupt processing overhead (the DRV8434S allows up to 500 kHz step).
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
int span_init(void) {
    int err;
    const struct device *span_limit_port = span1_limit_a_gpio.port;
    if (span_limit_port != span1_limit_b_gpio.port ||
            span_limit_port != span2_limit_a_gpio.port ||
            span_limit_port != span2_limit_b_gpio.port) {
        return -EIO;
    }
    if (!device_is_ready(span_limit_port)) {
        return -ENODEV;
    }
    if ((err = gpio_pin_configure_dt(&span1_limit_a_gpio, GPIO_INPUT)) ||
            (err = gpio_pin_configure_dt(&span1_limit_b_gpio, GPIO_INPUT)) ||
            (err = gpio_pin_configure_dt(&span2_limit_a_gpio, GPIO_INPUT)) ||
            (err = gpio_pin_configure_dt(&span2_limit_b_gpio, GPIO_INPUT))) {
        return err;
    }

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
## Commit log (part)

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2025-10-15 Import the v0.1 hardware and firmware.
2025-10-22 First draft of the new bed lift PCB.
2025-10-22 Finalize for production
2025-10-22 Add illustrations
2025-10-22 Add illustrations of the lift itself
2025-10-23 Fix errata in v0.2, reversed lift motor pins 2 and 3.
2025-11-03 Create v0.3 hardware from v0.2.
2025-11-04 Update v0.3 to address errata.
    Moved the board design and errata into a versioned documents.
    Added some photos of the bed.
2025-11-04 Clarify the workaround for the motor connector mismatch.
2025-11-19 Implemented initial scaffold for new firmware using Zephyr.
2025-11-19 Add todo for more capacitors
2025-11-22 Work in progress on the new firmware based on Zephyr RTOS.
2025-12-02 Allow lift to catch up after stop when desynchronized.
2025-12-02 Implement the span movement loop as high prority thread.
2025-12-03 Variable step frequency and stall learning.
    Stall detection does not work because there is too much jitter between
    steps issued over SPI. So this code will need to be rewritten to output
    steps with a hardware GPIO.
2025-12-03 Amend errata
2025-12-06 Rewrite step sequencer using PWM for accurate timing.
    Stall detection works now and the acoustics are much better.
2025-12-06 Amend errata for timer pins.
2025-12-07 Implement a simple menu system for rescuing the lift.
2025-12-08 Disable the fault interrupt handler.
    Avoid sharing the EXTI line with a different GPIO that's more important.
    Reduce code size.
2025-12-16 Implement the rest of the lift functionality.
    Implemented a PID control loop for the linear actuators.
    Improved error reporting.
    Resolved issues with the linear actuator hall sensors.
2025-12-17 Add an external monitoring interface over I2C.
    Improved error reporting.
    Enabled LTO to reduce flash size.
2025-12-22 Tuning and integration.
    Set stall threshold dynamically based on the speed of travel.
    Filter out brief stalls when the mechanism binds slightly.
    Allow individual span actuators to be disabled, span 1 is currently intermittent.
    Reduce the span actuator speed at the start and end of travel.
    Use slow decay during PWM to improve lift actuator torque and prevent
    voltage spikes.
2025-12-30 Perform a simple rainbow color wheel progress animation.
    Showing the actual progress as a color wasn't effective.
2026-01-04 Complete first draft of v1.0 hardware.
2026-01-04 Review BOM.
2026-01-06 Improve power distribution.
2026-01-13 Further refinement.
2026-01-14 Further refinement, ready for fabrication.
2026-01-14 Move new bed-lift hardware to v1 folder.
    Minor revisions will be performed in-situ without duplicating everything.
2026-01-15 Add updated photos and a video tour.
2026-01-15 Correct the BOOT0 pin polarity in the documentation.
2026-01-15 Include SMD models in the 3D renderings.
2026-01-15 Finalize for production of v1.0 revision.
2026-01-30 Prepare for development of the v1 firmware.
    Rearranged the project as a Zephyr West style workspace to be compatible
    with the latest version of Zephyr. Unfortunately Platform IO does not
    support building Zephyr 4.3 projects right now and we need the latest
    board files for the STM32C051.
    Deleted the v0.1 firmware altogether.
2026-02-01 Update firmware for v1 hardware.
    Updated pin assignments
    Decoupled lift and span sleep state.
    Added control of 5 V regulator.
    Added on-board "power" indicator.
    Added audible feedback.
    Enabled timer break function to stop lift immediately on faults.
2026-02-02 Enable span limit sensors and reduce speed during partial travel.
2026-02-03 Improve documentation, rearrange error codes.
2026-03-07 Refactoring and cleanup.
2026-03-07 Stop lift at ceiling level except for debugging.
2026-03-08 Add some slack to the span limit detection.
2026-03-08 Improve bed travel parameters for reliability.
2026-03-08 Add a mode to lock the lift into automatic movement.
    Rewrote the command dispatch to enable new features.
    Lengthened the time that the mode button must be held to access
    diagnostic modes to lessen the likelihood of accidental entry.
    Added a tone to facilitate blind menu navigation.
